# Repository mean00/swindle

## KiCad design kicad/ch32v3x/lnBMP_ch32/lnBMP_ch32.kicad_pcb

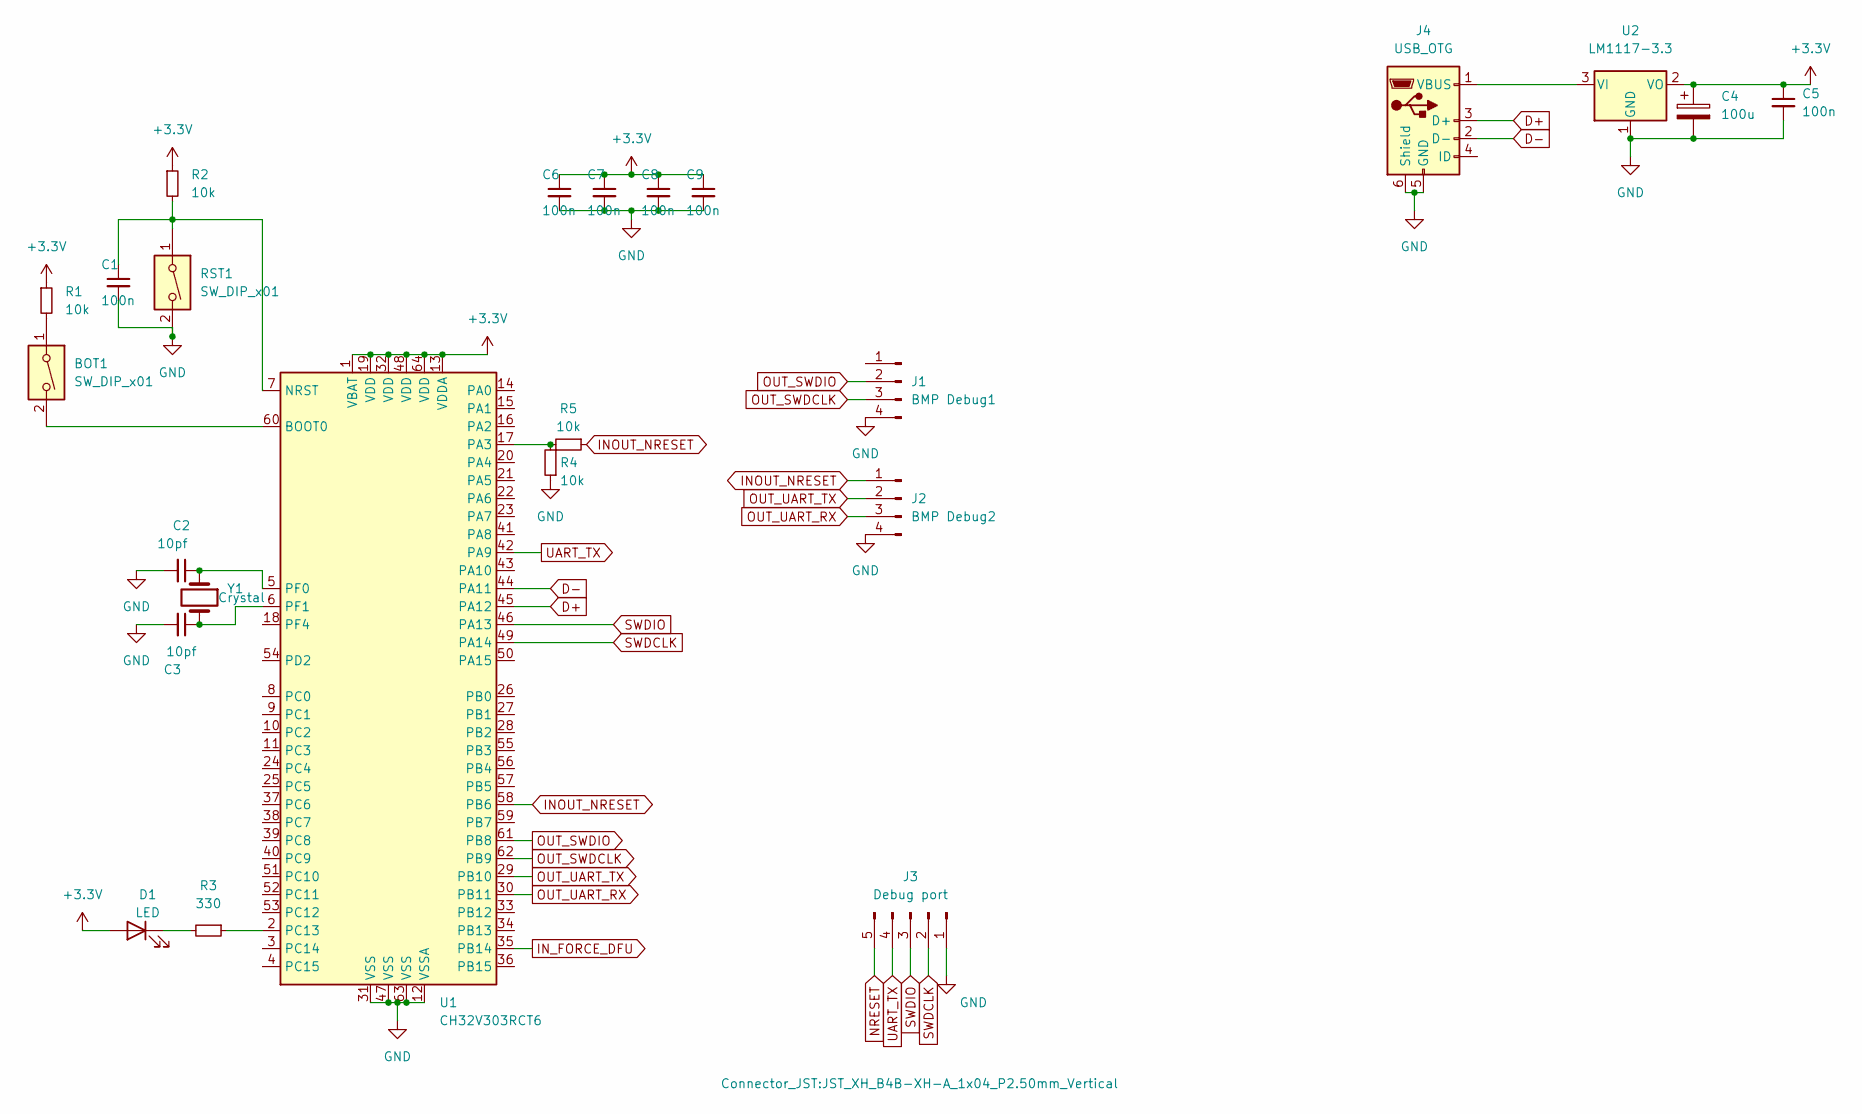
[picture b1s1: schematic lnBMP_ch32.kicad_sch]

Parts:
BOT1: SW_DIP_x01; SW_SPST_CK_RS282G05A3
C1, C5, C6, C7, C8, C9: 100n; R_0603_1608Metric
C2, C3: 10pf; R_0603_1608Metric
C4: 100u; CP_Radial_D4.0mm_P2.00mm
D1: LED; D_0805_2012Metric
J1: BMP Debug1; JST_XH_B4B-XH-A_1x04_P2.50mm_Vertical
J2: BMP Debug2; JST_XH_B4B-XH-A_1x04_P2.50mm_Vertical
J3: Debug port; JST_XH_B4B-XH-A_1x04_P2.50mm_Vertical
J4: USB_OTG; USB_Micro-B_Wuerth_629105150521
R1, R2, R4, R5: 10k; R_0603_1608Metric
R3: 330; R_0603_1608Metric
RST1: SW_DIP_x01; SW_SPST_CK_RS282G05A3
U1: CH32V303RCT6; LQFP-64_10x10mm_P0.5mm
U2: LM1117-3.3; SOT-223
Y1: Crystal; Crystal_HC49-U_Vertical

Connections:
+3.3V: C4.1, C5.1, C6.1, C7.1, C8.1, C9.1, D1.2 (A), R1.1, R2.1, U1.1 (VBAT), U1.13 (VDDA), U1.19 (VDD), U1.32 (VDD), U1.48 (VDD), U1.64 (VDD), U2.2 (VO); also elsewhere on the board
D+: J4.3 (D+), U1.45 (PA12)
D-: J4.2 (D-), U1.44 (PA11)
GND: C1.2, C2.2, C3.2, C4.2, C5.2, C6.2, C7.2, C8.2, C9.2, J1.4, J2.4, J3.1, J4.5 (GND), J4.6 (Shield), R4.1, RST1.2, U1.12 (VSSA), U1.31 (VSS), U1.47 (VSS), U1.63 (VSS), U2.1 (GND); also elsewhere on the board
INOUT_NRESET: J2.1, R5.1, U1.58 (PB6)
IN_FORCE_DFU: U1.35 (PB14); also elsewhere on the board
unnamed: BOT1.1, R1.2
unnamed: D1.1 (K), R3.2
unnamed: J4.1 (VBUS), U2.3 (VI)
unnamed: BOT1.2, U1.60 (BOOT0)
unnamed: C1.1, R2.2, RST1.1, U1.7 (NRST)
unnamed: R4.2, R5.2, U1.17 (PA3)
unnamed: R3.1, U1.2 (PC13)
unnamed: C2.1, U1.5 (PF0), Y1.1
unnamed: C3.1, U1.6 (PF1), Y1.2
OUT_SWDCLK: J1.3, U1.62 (PB9)
OUT_SWDIO: J1.2, U1.61 (PB8)
OUT_UART_RX: J2.3, U1.30 (PB11)
OUT_UART_TX: J2.2, U1.29 (PB10)
SWDCLK: J3.2, U1.49 (PA14)
SWDIO: J3.3, U1.46 (PA13)
UART_TX: J3.4, U1.42 (PA9)

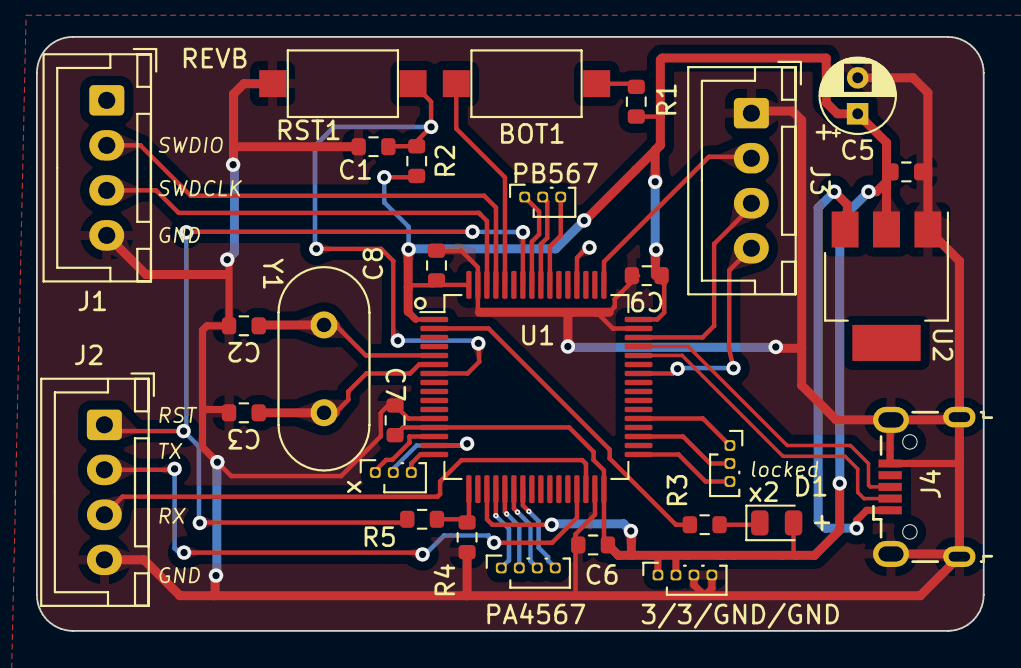
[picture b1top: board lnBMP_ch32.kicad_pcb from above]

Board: 2 copper layers, 52.6 x 33.0 mm, 29 parts (0 on the bottom side), 22 nets.

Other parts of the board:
3/3/GND/GND: PinSocket_1x04_P1.00mm_Vertical
PA4567: PinSocket_1x04_P1.00mm_Vertical
PB567: PinSocket_1x03_P1.00mm_Vertical
x, x2: PinSocket_1x03_P1.00mm_Vertical

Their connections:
+3.3V: 3/3/GND/GND.1, 3/3/GND/GND.2; also elsewhere on the board
GND: 3/3/GND/GND.3, 3/3/GND/GND.4; also elsewhere on the board
IN_FORCE_DFU: x2.2; also elsewhere on the board

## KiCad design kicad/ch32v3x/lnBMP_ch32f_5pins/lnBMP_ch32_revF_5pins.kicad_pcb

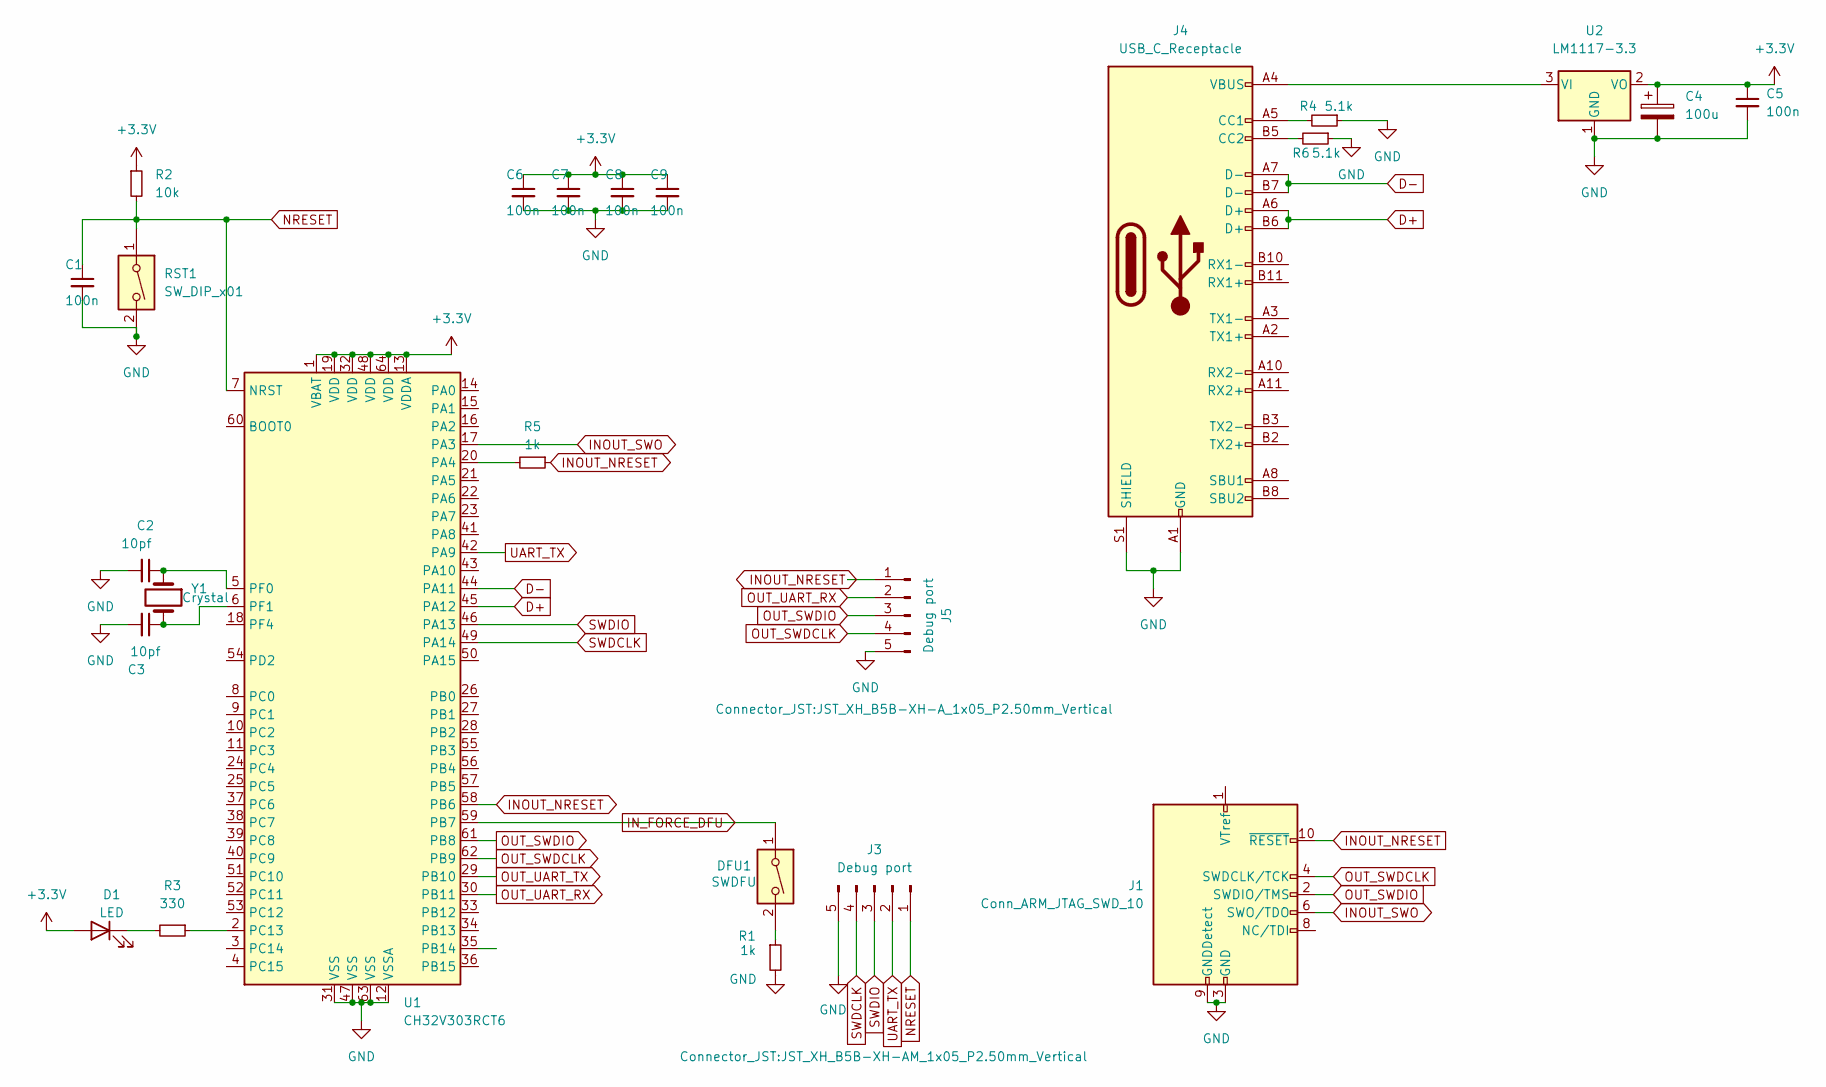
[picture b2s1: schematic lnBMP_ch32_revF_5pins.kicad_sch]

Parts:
C1, C5, C6, C7, C8, C9: 100n; R_0603_1608Metric
C2, C3: 10pf; R_0603_1608Metric
C4: 100u; CP_Radial_D4.0mm_P2.00mm
D1: LED; D_0805_2012Metric
DFU1: SWDFU; SW_SPST_CK_RS282G05A3
J1: Conn_ARM_JTAG_SWD_10; PinHeader_2x05_P1.27mm_Vertical_SMD
J3: Debug port; JST_XH_B5B-XH-AM_1x05_P2.50mm_Vertical
J4: USB_C_Receptacle; USB_C_Receptacle_Palconn_UTC16-G
J5: Debug port; JST_XH_B5B-XH-A_1x05_P2.50mm_Vertical
R1, R5: 1k; R_0603_1608Metric
R2: 10k; R_0603_1608Metric
R3: 330; R_0603_1608Metric
R4, R6: 5.1k; R_0603_1608Metric
RST1: SW_DIP_x01; SW_SPST_CK_RS282G05A3
U1: CH32V303RCT6; LQFP-64_10x10mm_P0.5mm
U2: LM1117-3.3; SOT-223
Y1: Crystal; Crystal_HC49-U_Vertical

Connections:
+3.3V: C4.1, C5.1, C6.1, C7.1, C8.1, C9.1, D1.2 (A), R2.1, U1.1 (VBAT), U1.13 (VDDA), U1.19 (VDD), U1.32 (VDD), U1.48 (VDD), U1.64 (VDD), U2.2 (VO); also elsewhere on the board
D+: J4.A6 (D+), J4.B6 (D+), U1.45 (PA12)
D-: J4.A7 (D-), J4.B7 (D-), U1.44 (PA11)
GND: C1.2, C2.2, C3.2, C4.2, C5.2, C6.2, C7.2, C8.2, C9.2, J1.3 (GND), J1.5 (GND), J1.9 (GNDDetect), J3.5, J4.A1 (GND), J4.A12 (GND), J4.B1 (GND), J4.B12 (GND), J4.S1 (SHIELD), J5.5, R1.2, R4.1, R6.1, RST1.2, U1.12 (VSSA), U1.31 (VSS), U1.47 (VSS), U1.63 (VSS), U2.1 (GND); also elsewhere on the board
INOUT_NRESET: J1.10 (~RESET), J5.1, R5.1, U1.58 (PB6)
INOUT_SWO: J1.6 (SWO/TDO), U1.17 (PA3)
IN_FORCE_DFU: DFU1.1, U1.59 (PB7)
NRESET: C1.1, J3.1, R2.2, RST1.1, U1.7 (NRST)
unnamed: D1.1 (K), R3.2
unnamed: DFU1.2, R1.1
unnamed: J4.A5 (CC1), R4.2
unnamed: J4.B5 (CC2), R6.2
unnamed: R5.2, U1.20 (PA4)
unnamed: R3.1, U1.2 (PC13)
unnamed: C2.1, U1.5 (PF0), Y1.1
unnamed: C3.1, U1.6 (PF1), Y1.2
unnamed: J4.A4 (VBUS), J4.A9 (VBUS), J4.B4 (VBUS), J4.B9 (VBUS), U2.3 (VI)
OUT_SWDCLK: J1.4 (SWDCLK/TCK), J5.4, U1.62 (PB9)
OUT_SWDIO: J1.2 (SWDIO/TMS), J5.3, U1.61 (PB8)
OUT_UART_RX: J5.2, U1.30 (PB11)
OUT_UART_TX: U1.29 (PB10)
SWDCLK: J3.4, U1.49 (PA14)
SWDIO: J3.3, U1.46 (PA13)
UART_TX: J3.2, U1.42 (PA9)

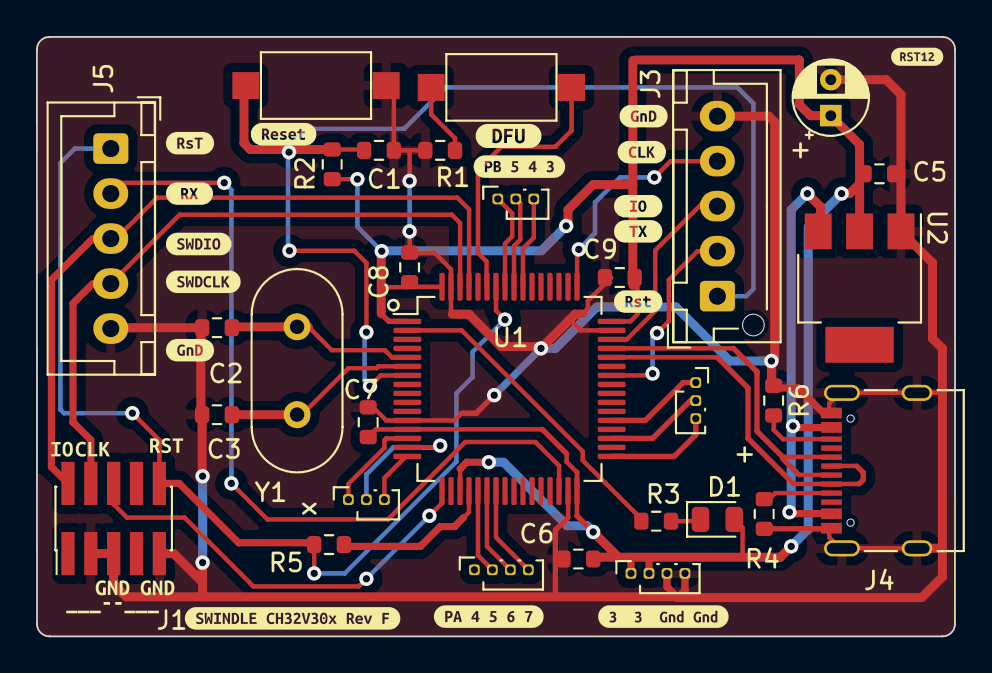
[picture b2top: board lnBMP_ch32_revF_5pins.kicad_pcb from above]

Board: 2 copper layers, 51.0 x 33.3 mm, 53 parts (0 on the bottom side), 23 nets.

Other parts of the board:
3/3/GND/GND: PinSocket_1x04_P1.00mm_Vertical
PA4567: PinSocket_1x04_P1.00mm_Vertical
PB567: PIN1X3; PinSocket_1x03_P1.00mm_Vertical
kibuzzard-65C1C7A6: G***; kibuzzard-65C1C7A6
kibuzzard-65C1C7F5: G***; kibuzzard-65C1C7F5
kibuzzard-65C1C8EE: G***; kibuzzard-65C1C8EE
kibuzzard-65C1C9D7: G***; kibuzzard-65C1C9D7
kibuzzard-65C1C92F: G***; kibuzzard-65C1C92F
kibuzzard-65C1C718: G***; kibuzzard-65C1C718
kibuzzard-65C1C789, kibuzzard-65C1C789#2: G***; kibuzzard-65C1C789
kibuzzard-65C1C805: G***; kibuzzard-65C1C805
kibuzzard-65C1C918: G***; kibuzzard-65C1C918
kibuzzard-65C1C972: G***; kibuzzard-65C1C972
kibuzzard-65C281E1: G***; kibuzzard-65C281E1
kibuzzard-65C281F8: G***; kibuzzard-65C281F8
kibuzzard-65C13741: G***; kibuzzard-65C13741
kibuzzard-65D842E2: G***; kibuzzard-65D842E2
kibuzzard-65D8420C: G***; kibuzzard-65D8420C
kibuzzard-66C043C9: G***; kibuzzard-66C043C9
kibuzzard-66C0434B: G***; kibuzzard-66C0434B
kibuzzard-66C0437E: G***; kibuzzard-66C0437E
kibuzzard-66C04316: G***; kibuzzard-66C04316
kibuzzard-66C04342: G***; kibuzzard-66C04342
kibuzzard-66C04372: G***; kibuzzard-66C04372
kibuzzard-664C331A: G***; kibuzzard-664C331A
x, x2: PinSocket_1x03_P1.00mm_Vertical

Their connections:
+3.3V: 3/3/GND/GND.1, 3/3/GND/GND.2; also elsewhere on the board
GND: 3/3/GND/GND.3, 3/3/GND/GND.4; also elsewhere on the board

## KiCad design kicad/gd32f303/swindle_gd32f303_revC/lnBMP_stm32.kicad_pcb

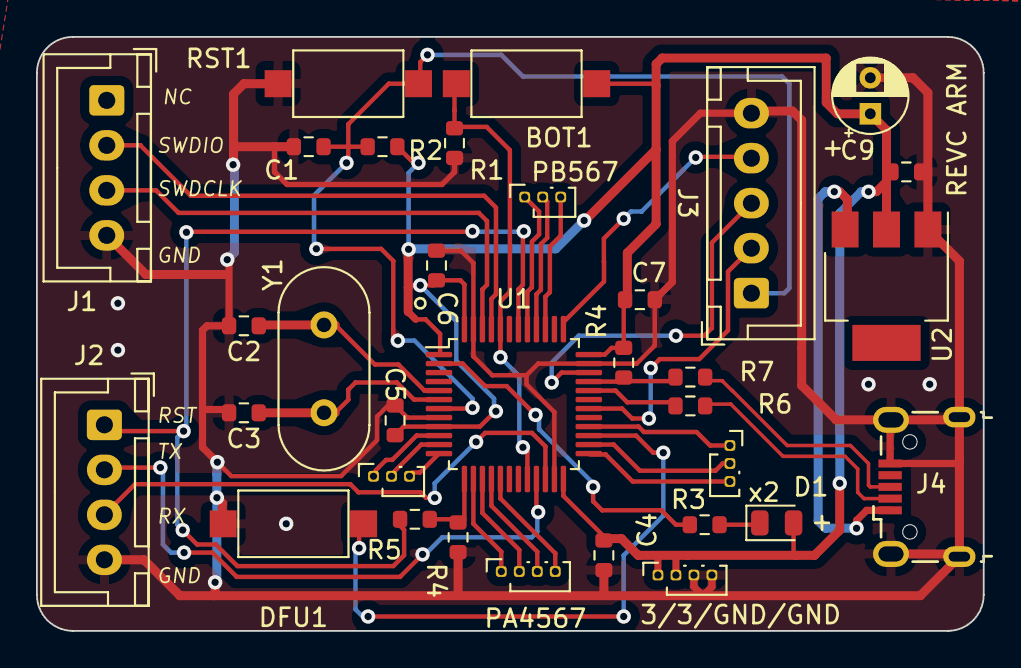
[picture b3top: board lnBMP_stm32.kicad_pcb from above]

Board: 2 copper layers, 52.6 x 33.0 mm, 32 parts (0 on the bottom side), 23 nets.

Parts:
3/3/GND/GND: PinSocket_1x04_P1.00mm_Vertical
BOT1: SW1; SW_SPST_CK_RS282G05A3
C1, C4, C5, C6, C7, C9: 100n; R_0603_1608Metric
C2, C3: 10pF; R_0603_1608Metric
C8: C_Polarized; CP_Radial_D4.0mm_P2.00mm
D1: LED; D_0805_2012Metric
DFU1: SW_DIP_x01; SW_SPST_CK_RS282G05A3
J1: BMP Debug1; JST_XH_B4B-XH-A_1x04_P2.50mm_Vertical
J2: BMP Debug2; JST_XH_B4B-XH-A_1x04_P2.50mm_Vertical
J3: Debug port; JST_XH_B5B-XH-A_1x05_P2.50mm_Vertical
J4: USB_OTG; USB_Micro-B_Wuerth_629105150521
PA4567: PinSocket_1x04_P1.00mm_Vertical
PB567: PinSocket_1x03_P1.00mm_Vertical
R1, R2: 10k; R_0603_1608Metric
R3: 330; R_0603_1608Metric
R4: R_Small; R_0603_1608Metric
R4#2: 1.2k; R_0603_1608Metric
R5: 1k; R_0603_1608Metric
R6, R7: 22; R_0603_1608Metric
RST1: SW2; SW_SPST_CK_RS282G05A3
U1: STM32F103CBTx; LQFP-48_7x7mm_P0.5mm
U2: LM1117-3.3; SOT-223
Y1: Crystal; Crystal_HC49-U_Vertical
x2: PinSocket_1x03_P1.00mm_Vertical

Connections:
+3.3V: 3/3/GND/GND.1, 3/3/GND/GND.2, BOT1.1, C4.1, C5.1, C6.1, C7.1, C8.1, C9.1, D1.2 (A), R2.1, R4#2.1, U1.1 (VBAT), U1.9 (VDDA), U1.24 (VDD), U1.36 (VDD), U1.48 (VDD), U2.2 (VO)
D+: J4.3 (D+), R7.1
D-: J4.2 (D-), R6.1
GND: 3/3/GND/GND.3, 3/3/GND/GND.4, C1.2, C2.2, C3.2, C4.2, C5.2, C6.2, C7.2, C8.2, C9.2, DFU1.2, J1.4, J2.4, J3.5, J4.5 (GND), J4.6 (Shield), R1.2, R4.1, RST1.2, U1.8 (VSSA), U1.23 (VSS), U1.35 (VSS), U1.47 (VSS), U2.1 (GND)
INOUT_NRESET: J2.1, R5.1, U1.42 (PB6)
IN_FORCE_DFU: DFU1.1, U1.27 (PB14)
NRST: C1.1, J3.1, R2.2, RST1.1, U1.7 (NRST)
unnamed: D1.1 (K), R3.2
unnamed: J4.1 (VBUS), U2.3 (VI)
unnamed: BOT1.2, R1.1, U1.20 (PB2), U1.44 (BOOT0)
unnamed: R4.2, R5.2, U1.13 (PA3)
unnamed: R6.2, U1.32 (PA11)
unnamed: R4#2.2, R7.2, U1.33 (PA12)
unnamed: R3.1, U1.2 (PC13)
unnamed: C2.1, U1.5 (PD0), Y1.1
unnamed: C3.1, U1.6 (PD1), Y1.2
OUT_SWDCLK: J1.3, U1.46 (PB9)
OUT_SWDIO: J1.2, U1.45 (PB8)
OUT_UART_RX: J2.3, U1.22 (PB11)
OUT_UART_TX: J2.2, U1.21 (PB10)
SWDCLK: J3.4, U1.37 (PA14)
SWDIO: J3.3, U1.34 (PA13)
UART_TX: J3.2, U1.30 (PA9)
